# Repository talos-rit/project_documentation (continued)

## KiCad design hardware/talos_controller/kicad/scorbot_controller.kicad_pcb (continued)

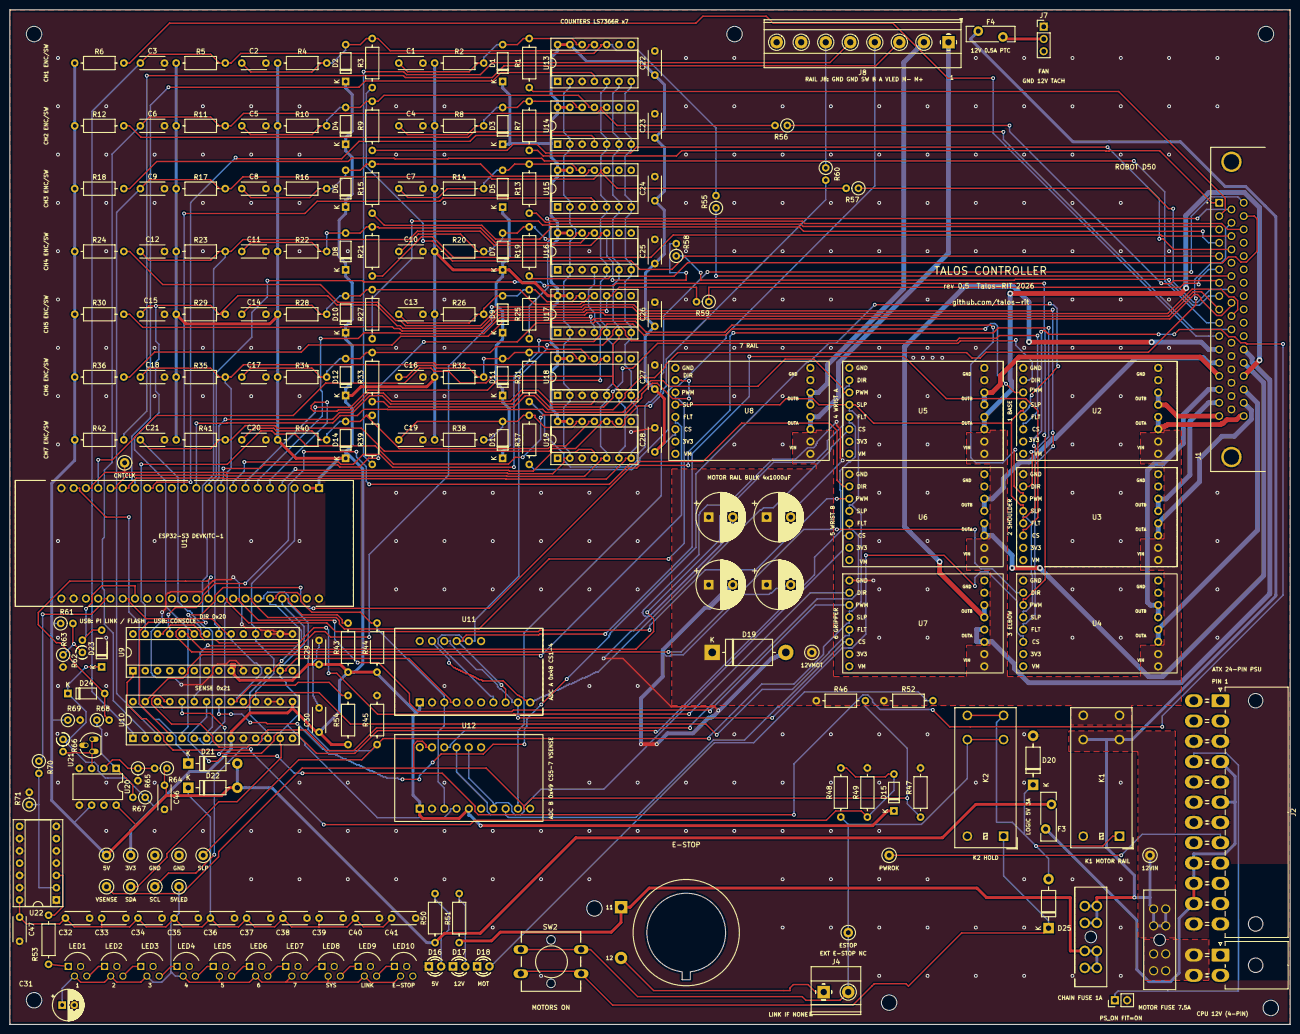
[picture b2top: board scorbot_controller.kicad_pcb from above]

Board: 2 copper layers, 265.0 x 210.0 mm, 231 parts (0 on the bottom side), 147 nets.

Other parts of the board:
H1, H2, H3, H4, H9, H10, H11: MountingHole_3.2mm_M3

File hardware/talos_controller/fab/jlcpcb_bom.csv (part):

Comment,Designator,Footprint,JLCPCB Part #,Design part (Digi-Key BOM),Note
1nF,"C1,C2,C4,C5,C7,C8,C10,C11,C13,C14,C16,C17,C19,C20",C_Disc_D5.0mm_W2.5mm_P5.00mm,C2761735,TDK FG28C0G1H102JNT06,"Dersonic CD1H102KC9BER1D100 1 nF 50 V X7R +-10 %, 5.08 mm; C20754723 (Y5P) not found; encoder RC tolerates +-30 %; verify stock"
100nF,"C22,C23,C24,C25,C26,C27,C28,C29,C30,C32,C33,C34,C35,C36,C37,C38,C39,C40,C41",C_Disc_D5.0mm_W2.5mm_P5.00mm,C254085,TDK FG28X7R1H104KNT06,"Dersonic CC1H104MC1FD3F6C10MF 100nF 50V Y5V disc, P=5.08 mm, decoupling only (19)"
100nF X7R,"C3,C6,C9,C12,C15,C18,C21,C46,C47",C_Disc_D5.0mm_W2.5mm_P5.00mm,C342794,TDK FG28X7R1H104KNT06,"the design part itself (TDK X7R, 5 mm): the switch-line RC (C3-C21), U20's (C46) and U22's (C47) decoupling; was hand-fitted only for the dielectric"
100uF 25V,C31,CP_Radial_D6.3mm_P2.50mm,C165558,Panasonic EEU-FR1E101,"SamYoung NXA25V100M6.3*11 2.5TP, 6.3 x 11 mm, 2.5 mm pitch, 105 C 5000 h: matched at order 2026-11-11, 8,132 in stock (the design part EEU-FR1E101, C264049, had 1); polarised: check the stripe in JLCPCB's placement preview"
1000uF 25V,"C42,C43,C44,C45",CP_Radial_D10.0mm_P5.00mm,C2960400,Panasonic EEU-FR1E102,"HRK CD110 25V 1000uF 10x20 mm, 5 mm pitch; alternative C231201 (Lelon RXK, 10x20). Not the 12.5 mm can"
BAT42,D15,D_DO-35_SOD27_P7.62mm_Horizontal,C2798198,Vishay BAT85,"ST BAT42 on D15 ONLY (e-stop sense node into the MCP23017: VDD+0.6 V, IIK +-20 mA); NOT on D1-D14, D23, D24; polarised: check the band end in JLCPCB's placement view"
green,"D16,D17",LED_D3.0mm,C85161,Kingbright WP710A10GD,"Everlight 204-10SYGD/S530-E3 3 mm yellow-green, 2.54 mm pitch; no sheet for it in fab/datasheets (the Kingbright sheets cover only the WP710A10 parts); check the lamp polarity in JLCPCB's placement preview (cathode = the short lead = pad 1, the square pad"
yellow,D18,LED_D3.0mm,C85160,Kingbright WP710A10YD,"Everlight 204-10UYD/S530-A3-L 3 mm yellow, stock not seen; else hand-fit the Kingbright; check the lamp polarity in JLCPCB's placement preview (cathode = the short lead = pad 1, the square pad"
1.5KE16A,D19,D_DO-201AD_P15.24mm_Horizontal,C3034403,Littelfuse 1.5KE16A,matched by JLCPCB (Sept 16); not found by the 2026-10-22 search; no substitute accepted
1N4007,"D20,D25",D_DO-41_SOD81_P10.16mm_Horizontal,C78736,onsemi 1N4007G,"MCC 1N4007-TP DO-41; D20 coil flyback, D25 K2 hold: silicon, never a Schottky; check the band end of D20 and D25 in JLCPCB's placement preview"
1N5819,D21,D_DO-41_SOD81_P10.16mm_Horizontal,C2474,onsemi 1N5819G,"MDD 1N5819 (D22 is a link, hand-fitted); polarised: check the band end in JLCPCB's placement view"
ATO holder,"F1,F2",FuseHolder_Blade_ATO_Littelfuse_FLR_178.6165,C207061,Littelfuse 178.6165.0001,"Littelfuse 178.6165.0002, the same holder as the .0001 in 500-piece packing (drawing 178.6165.0000 rev H): matched at order 2026-11-11, 2,129 in stock (C207060 had 1); the fuses (F1 028707.5PXCN, F2 0287001.PXCN) are pushed in by hand"
3 A PTC,F3,Fuse_Bourns_MF-RG400,C208487,Littelfuse RUEF300,"Bourns MF-R300 ONLY if its sheet gives R1max <= 0.08 Ohm and 5.1 mm leads (the 5 V budget used 20-80 mOhm); else hand-fit RUEF300; JLCPCB's listing gives R1max 80 mOhm and 5.1 mm leads: condition met, placed"
0.5 A PTC,F4,Fuse_Bourns_MF-RG400,C76399,Littelfuse RXEF050,the design part
E-STOP ext (NC),J4,"TerminalBlock_Phoenix_MKDS-1,5-2-5.08_1x02_P5.08mm_Horizontal",C480516,"Phoenix Contact MKDS 1,5/ 2-5,08 (1715721)","the design part: 5.08 mm, 0.9 x 0.9 mm pins, 1.3 mm hole (fab/datasheets Phoenix_Contact-1715721); matched at order 2026-11-11, 2,166 in stock; JLCPCB's automatic matcher does not assign this code even though a manual search finds it in stock: at upload, Search C480516 and Select by hand; alternatives if that bothers you: C5183929 (the same Phoenix part under a second listing) or C2915639 (the DORABO DB128V-5.08-2P, the 2-pole sibling of J8, covered by the same drawing)"
FAN 12 V,J7,PinHeader_1x03_P2.54mm_Vertical,C49257,generic PinHeader 1x03,BOOMELE 2.54-1*3P male header
RAIL,J8,"TerminalBlock_Phoenix_MKDS-1,5-8-5.08_1x08_P5.08mm_Horizontal",C5143711,"Phoenix Contact MKDS 1,5/ 8-5,08 (1715789)","DORABO DB128V-5.08-8P-GN-S, accepted on its drawing 2026-11-10 (fab/datasheets/DORABO DB128V-5.08-XXP-C-S drawing (C5143711).pdf; 2,062 in stock; the design part Phoenix 1715789 is not at LCSC and stays the hand-fit fallback (Digi-Key)"
PS_ON (fit = on),JP1,PinHeader_1x02_P2.54mm_Vertical,C32713268,generic PinHeader 1x02 + jumper,"hanxia HX PZ2.54-1x2P ZZ, straight 1x2 male header (2.5 mm insulator, 6 mm pin, 3 mm tail): matched at order 2026-11-11, 183,211 in stock; the shunt is fitted by hand"
G5RL-1A-E-HR 12V 16A,"K1,K2",Relay_SPST_Omron_G2RL-1A-E,C231374,Omron G2RL-1A-E DC12,"Omron G5RL-1A-E-HR DC12: the accepted drop-in for the design part G2RL-1A-E DC12: same footprint and coil (12 V, 360 Ohm, 33 mA), 16 A NO contact, inrush-rated (high-inrush model); matched at order 2026-11-12, 130 in stock. If the G2RL is back in stock it is equally fine. Check the relay orientation in JLCPCB's placement preview (a different model than the G2RL's); the pin pattern is asymmetric, so a wrong rotation shows as pins off the pads. Rejected lookalikes: G2RL-1A-E-CN (C469120), plain G5RL-1A-E (C122874)"
1k,"R1,R3,R7,R9,R13,R15,R19,R21,R25,R27,R31,R33,R37,R39,R50,R52,R55,R56,R57,R58,R59,R60,R69",R_Axial_DIN0207_L6.3mm_D2.5mm_P10.16mm_Horizontal; upright designators: R_Axial_DIN0207_L6.3mm_D2.5mm_P2.54mm_Vertical,C57435,Yageo MFR-25FBF52-1K,"UNI-ROYAL MFR0W4F1001A50 1 % metal film (C53431608 not found); UPRIGHT (2.54 mm pitch) designators R55,R56,R57,R58,R59,R60,R69: JLCPCB forms them on end, the placement preview shows the 2.54 mm pairs; one line since 2026-11-11 so the upload raises no duplicate-part warning (the two lines matched the same code)"
10k,"R2,R4,R5,R8,R10,R11,R14,R16,R17,R20,R22,R23,R26,R28,R29,R32,R34,R35,R38,R40,R41,R47,R49,R54,R71",R_Axial_DIN0207_L6.3mm_D2.5mm_P10.16mm_Horizontal; upright designators: R_Axial_DIN0207_L6.3mm_D2.5mm_P2.54mm_Vertical,C57436,Yageo MFR-25FBF52-10K,"UNI-ROYAL MFR0W4F1002A50 1 % (Yageo C1519255 out of stock); UPRIGHT (2.54 mm pitch) designators R71: JLCPCB forms them on end, the placement preview shows the 2.54 mm pairs; one line since 2026-11-11 so the upload raises no duplicate-part warning (the two lines matched the same code)"
47,"R6,R12,R18,R24,R30,R36,R42",R_Axial_DIN0207_L6.3mm_D2.5mm_P10.16mm_Horizontal,C58604,Yageo MFR-25FBF52-47R,"UNI-ROYAL MFR0W4F470JA50 47 Ohm (the listing says 1 % although the J in the code usually means 5 %; encoder LED series, either is fine): matched at order 2026-11-11, 4,060 in stock"
2.2k,"R43,R44,R45,R51,R66,R67",R_Axial_DIN0207_L6.3mm_D2.5mm_P10.16mm_Horizontal; upright designators: R_Axial_DIN0207_L6.3mm_D2.5mm_P2.54mm_Vertical,C58595,Yageo MFR-25FBF52-2K2,"UNI-ROYAL MFR0W4F2201A50 1 %: matched at order 2026-11-11, 2,397 in stock; UPRIGHT (2.54 mm pitch) designators R66,R67: JLCPCB forms them on end, the placement preview shows the 2.54 mm pairs; one line since 2026-11-11 so the upload raises no duplicate-part warning (the two lines matched the same code)"
39k,R46,R_Axial_DIN0207_L6.3mm_D2.5mm_P10.16mm_Horizontal,C1369871,Yageo MFR-25FBF52-39K,"Yageo MFR-25FBF52-39K, the design part: matched by JLCPCB at order 2026-11-11"
30k,R48,R_Axial_DIN0207_L6.3mm_D2.5mm_P10.16mm_Horizontal,C58652,Yageo MFR-25FBF52-30K,"UNI-ROYAL MFR0W4F3002A50, title only: confirm value and stock"
330,"R53,R70",R_Axial_DIN0207_L6.3mm_D2.5mm_P10.16mm_Horizontal; upright designators: R_Axial_DIN0207_L6.3mm_D2.5mm_P2.54mm_Vertical,C119313,Yageo MFR-25FBF52-330R,"CCO MF1/4W-330R 1 %; UPRIGHT (2.54 mm pitch) designators R70: JLCPCB forms them on end, the placement preview shows the 2.54 mm pairs; one line since 2026-11-11 so the upload raises no duplicate-part warning (the two lines matched the same code)"
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
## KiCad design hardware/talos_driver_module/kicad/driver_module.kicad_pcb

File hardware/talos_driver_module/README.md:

# Talos driver module, rev 0.1

A plug-in motor driver for the [Talos controller board](../talos_controller/README.md). It fits the controller's driver sockets
in place of a Pololu G2 18v17: the same 33 × 20 mm outline, the same sixteen pins, the same meaning on every pin the controller
uses. One module drives one brushed DC motor from the controller's 12 V motor rail. It is built from a TI DRV8701E gate driver,
two AO4882 dual MOSFETs as the H-bridge and a 20 mΩ shunt, all surface-mount on the top side of a two-layer board, so a board
house can build it complete except for the two pin strips.

The reason it exists is cost. The G2 is a 17 A general-purpose driver at about USD 45; a Scorbot joint motor needs 2 to 3 A.
Sized for that, ten assembled modules were quoted by JLCPCB on 13 November 2026 at USD 49.22 on lead-free HASL and USD 64.84 on
ENIG, before shipping: about USD 5 and USD 6.50 a module. A batch of twenty is estimated at about USD 3.40 a module.

> **Status, 13 November 2026.** First design, checked on paper only: design-rule check, the board's connections against the
> schematic, a recalculation of the copper's resistance, loops and heating, and the placement file pad by pad against JLCPCB's own
> footprints. No module has been built, powered or measured, and every figure below is a data-sheet value or an estimate. The
> files are fit for a small prototype batch, not for a robot:
> build a few, run the bench tests in section 6 next to a real G2, and only then put one on an arm. The limits and the open
> questions are in section 7.

Left to right: the logic pin row with a white bar beside it; the passives and the DRV8701E gate driver (U1); the two MOSFET
pairs Q2 and Q1 with the shunt R1 above them and the supply capacitors C1, C2 below; the power pin row. The round pads are test
points.

## What is in this folder

| File | What it is |
| --- | --- |
| `README.md` | this guide |
| `parts.md` | the parts list with the substitution rules |
| `fab/driver_module_rev0.1_gerbers.zip` and `.sha256` | the manufacturing files (Gerbers and drill files) |
| `fab/jlcpcb_bom.csv`, `fab/jlcpcb_cpl.csv` | the BOM and placement files for JLCPCB's assembly service |
| `fab/hand_assembled.csv` | what the assembly service does not place: the pin strips, the spare resistor position, the test pads |
| `schematic.pdf` | the schematic |
| `assembly_map.pdf` | every part's position with its reference and value, pin 1 marks, the pin names |
| `images/` | the board's top and bottom views and the assembly map as pictures |
| `kicad/` | the KiCad project: board, schematic, design rules, the project's footprint library. KiCad 7 format; later versions open and upgrade it |

## How it compares with the Pololu G2 18v17

| | Pololu G2 18v17 | This module |
| --- | --- | --- |
| Outline and pins | 1.3 × 0.8 in, two rows of eight | the same holes and outline |
| Supply | 6.5 to 30 V | the controller's 12 V rail (10 to 13 V); parts rated 40 V or more |
| Continuous current | 17 A | designed for 3 A, unproven: plan on 2 A until test 4 has been run (section 7) |
| Current limit | about 40 A unless a resistor is added | fixed by two resistors: 3.6 A typical, 2.5 to 4.5 A across part tolerances |
| Current-sense pin | about 20 mV/A plus about 50 mV | 19.7 mV/A plus 49 mV, by design |
| Sleep, fault, PWM and direction pins | | the same behaviour by design; the G2's published figures match the same TI driver |
| 3V3 and VM pins | outputs | pins present, not connected |
| Reverse-supply protection | yes | none |
| Over-temperature protection of the MOSFETs | none | none |
| Status | a tested product | untested |

What you give up is headroom and a proven product. The G2's MOSFETs are far larger than a Scorbot needs, which is what makes it
forgiving; this module has a few amps of margin, no more. It suits this controller and these motors, not a general 17 A job.

## 1. Order the boards

Upload `fab/driver_module_rev0.1_gerbers.zip` to JLCPCB as it is (check it against the `.sha256` file if it was copied around).

| Option | Choose |
| --- | --- |
| Layers, size | 2 layers; 33.02 × 20.32 mm is read from the files |
| Thickness, copper | 1.6 mm, 1 oz |
| Colour | green: the Economic assembly service offers ENIG on green boards only |
| Surface finish | ENIG gives flat pads under U1 (0.5 mm pitch) and cost USD 15.62 more for ten in our quote. Lead-free HASL is the cheaper choice and within what JLCPCB states for this pitch |
| Mark on PCB | have the order number left off, or put on the underside; the top has no room for it |
| Quantity | 5 is the minimum for bare boards; the Economic assembly service takes 2 to 50 |

**Assembly.** Tick PCB assembly, Economic, top side. Before paying, check that the quote page says "Economic PCBA Price": our
first quote had slipped to the Standard service, which charged about USD 36 more for the same ten modules. No panel, edge rails or fiducials are needed for a board this size. Upload
`fab/jlcpcb_bom.csv` as the BOM and `fab/jlcpcb_cpl.csv` as the placement file; every BOM line carries a JLCPCB part number.
Three part types are from the Extended library (U1, the MOSFETs, the shunt), which adds a fee per type.

**Check the placement preview before paying.** A chip turned by a quarter turn passes every automatic check and ruins the
batch. In the preview, the pin 1 dot of U1, Q1 and Q2 must sit where `assembly_map.pdf` has its red dots: for U1 the corner
nearest C3, for Q1 and Q2 the pad at the triangle on the silkscreen. The rotations in the placement file were computed from
JLCPCB's own library footprints for these parts (as they were on 13 November 2026), but the preview is the final word. Order the
files as they are: if a part is substituted in the order form, look at the preview again.

## 2. Parts

`parts.md` lists every part. The assembly service fits all of them except the two 1 × 8 pin strips, which you buy and solder
yourself. The position R3B stays empty.

## 3. Assemble

1. Push the two pin strips into a spare socket or a breadboard, long pins down, so they stand square and at the right spacing.
2. Lay the module on them, parts up. The silkscreen names each pin on both sides; the logic row is the side with the small parts.
3. Solder all sixteen pins from the top.
4. Look at the three chips under a magnifier for solder bridges before the first power.

Fitted this way the module stands about 11 mm above the controller, as a G2 on its own headers does.

**Before the first power.** Under a magnifier on every assembled module: U1's dot at the corner nearest C3, the dots of Q1 and Q2
at their triangles, no solder bridge along U1's four rows. With a multimeter: no short from GND to VIN, to OUTA or to OUTB. Then
power it for the first time from a bench supply with a current limit.

**Finding the test pads.** Only TP2, TP3 and TP5 are named on the board. The label "R3B" above the pad at the lower left
belongs to the empty resistor position beside it; that pad is TP6. The assembly map names every pad.

**Plugging a module in.** A module turned round still fits the socket, and so does one shifted by a pin; either destroys it,
or shorts the motor rail, the moment the rail comes on. With the rail off: the logic row (the white bar on the top of the
module runs along it, beside its pin names) goes to the socket's logic row, every pin sits in its own hole with none hanging
out, then power. Pull a module out by its two short ends, where the pins are; three small parts that set the current limit sit
close to one long edge.

## 4. Pins

Logic row, in socket order:

| Pin | Direction | What it does |
| --- | --- | --- |
| GND | | ground, common with the power row |
| DIR | in | direction: high drives OUTA high and OUTB low |
| PWM | in | 3.3 V logic. High drives the motor, low brakes it (both outputs low). 20 kHz in the firmware; the driver accepts up to 100 kHz and 100 % duty |
| SLP | in | low puts the driver to sleep: outputs open, under 15 µA from the rail at room temperature (data sheet). The module has no pull-up; the controller drives the line and holds it low at rest |
| FLT | out | open drain, low while the driver reports a fault. Never driven high; the controller supplies the pull-up |
| CS | out | motor current while driving: 19.7 mV/A plus 49 mV. 0 V while braking and asleep |
| 3V3 | | not connected |
| VM | | not connected |

Power row: GND (two pins), OUTB (two), OUTA (two), VIN (two).

## 5. Firmware

Nothing changes against a G2. The controller firmware keeps its defaults: PWM 20 kHz, current sense 20 mV/A with a 50 mV offset,
and the 5 % minimum duty for a current reading (`SC_PWM_FREQ_HZ`, `SC_CS_MV_PER_A`, `SC_CS_OFFSET_MV`, `SC_CS_MIN_DUTY_PCT` in
`idf.py menuconfig`). Modules and G2s can share a board.

**R3A or R3B.** The current-sense pin needs its 50 mV offset from somewhere. R3A takes it from the PWM pin, so the offset is there
only while the bridge drives and the pin reads 0 V in the PWM off-time: this is what the firmware assumes, and it is the fitted
position. R3B takes it from the driver's 3.3 V supply, so the offset stays through the off-time: this is what TI's data sheet
suggests a real G2 does. Measure a real G2 first (test 1 below). If it holds its offset in the off-time, the firmware's current
model has to change for the G2 anyway, and a batch of modules is then built with R3B fitted instead of R3A. Never fit both.

## 6. Bench tests before first use

Do these with one module and one real G2 side by side in a controller, each on the same type of motor, with a clamp meter on a
motor lead and an oscilloscope. Start from a bench supply with a current limit, not from the ATX supply. Never plug a module
into a live rail. Do the edge check of test 2 at a low current before anything that reaches the current limit (tests 3 to 5).

| Test | What to do | Expect |
| --- | --- | --- |
| 1. Current-sense pin and supply | On the G2 first: scope CS at 25, 50 and 100 % duty, at rest and at 2 A, during the on-time and the off-time. Then the same on the module, up to 4 A. While the module drives 3 A, also scope the supply across its VIN and GND pins | Module: 19.7 mV/A ± 3 % plus 49 mV while driving, under 2 mV in the off-time. Note what the G2 does in the off-time (section 5). Supply at the module: ripple under about 0.1 V at the PWM frequency, ringing of a few tenths of a volt after each edge (estimates); much more means the module needs a capacitor of its own |
| 2. Direction, brake and edges | DIR high and low, PWM at 0, 50 and 100 %. Then, at the current limit, scope U1's pins 18 and 23 (the switch nodes) and pin 21 (the sense input) against U1's centre pad with a short spring ground | Same motor direction as the G2; both outputs low with PWM low. The switch nodes stay above −2 V and the sense input within ±1 V at the edges; if not, the gate drive has to be slowed (R6) before the module is used |
| 3. Current limit | Stall the motor at 100 % duty with a current probe on the lead | The current holds between 2.5 and 4.5 A (3.6 A typical). Write the figure on the module |
| 4. Temperature | 3 A for 30 minutes inside the enclosure, in both directions (DIR low first: it is expected to run hotter), with a thermocouple on Q2's pins 5 and 6, once with warm modules in the neighbouring sockets. Then a 5-minute stall at 70 % duty | MOSFET case under 120 °C; no fault. This test decides the continuous rating. If the stall runs hotter, the firmware's stall detection is what protects the module |
| 5. Faults | From the current-limited supply, with the scope on test pad TP4 (the top of the shunt): short OUTA to OUTB through a switch; lower the supply below 6 V | FLT goes low and the firmware reports a driver fault; FLT releases afterwards; no damage. If TP4 peaks above 1 V in the short, change R8 to 100 Ω before going further |
| 6. Sleep and power-up | Switch SLP a hundred times with the rail on; switch the rail on and off with SLP low and with SLP high; watch FLT on the scope | Outputs open and CS at 0 V asleep. Record every FLT pulse: the driver pulls FLT low while its supply is under about 6 V, and the firmware must not treat that as a fault |
| 7. Back-drive | With SLP low, turn the motor fast by hand | Nothing but a small rise of the rail; module undamaged |

## 7. Limits and open questions

- **Nothing has been built.** The first batch is the first test of every footprint and of the layout.
- **3 A continuous is unproven.** A simple estimate puts the hottest MOSFET junction at about 95 °C at 3 A and 40 °C ambient. A
  model of the routed copper puts it at 105 to 128 °C when no heat leaves through the pins, higher still in dead air between
  neighbours, and at 87 to 102 °C when the pins carry heat into the controller. Neither is a measurement; test 4 is. Until it has
  been run, treat the module as a 2 A part; the controller firmware's per-joint current limits are 1.5 to 2.0 A.
- **The current limit of a given module lies between 2.5 and 4.5 A.** At the top of that range a held stall is estimated to
  overheat the MOSFETs within about two minutes, so the firmware's stall and over-current detection are part of the protection.
- **No over-temperature protection of the MOSFETs.** The driver chip shuts down at 150 °C of its own die only. The G2 is the same.
- **A short from an output to ground is detected only above roughly 28 to 65 A.** A partial short to the robot's frame can destroy a MOSFET
  without a fault report. A short across the motor is detected.
- **No large capacitor on the module.** A G2 carries a 150 µF electrolytic, the tall cylinder on most driver boards. This module
  has only ceramic capacitors (C1, C2, C10, C11) and relies on the controller's four 1000 µF capacitors, which sit on the motor
  rail a few centimetres from the sockets. By estimate the supply ripple at the module is under 0.1 V; test 1 measures it. Used
  anywhere but in this controller, the module needs a few hundred µF close to its VIN and GND pins.
- **No reverse-supply protection.** A bench supply can be connected backwards, and a module plugged in turned round sees the
  rail backwards (section 3). A G2 survives that; this module does not.
- **The FLT line during power-up.** The driver holds FLT low while the motor rail is below about 6 V, which happens at every
  MOTORS ON, e-stop and rail decay. The G2 is expected to do the same. Ignoring FLT while the drives are off is not yet
  implemented in the controller firmware.
- **The current reading includes the ground drop of the socket contacts,** on this module and on a G2 alike. If it matters, the
  cure is a per-board scale in the firmware.
- **Second sources.** The DRV8701E is a TI part with no equivalent. The AO4882 has pin-compatible copies with different
  on-resistance; see `parts.md` before substituting.

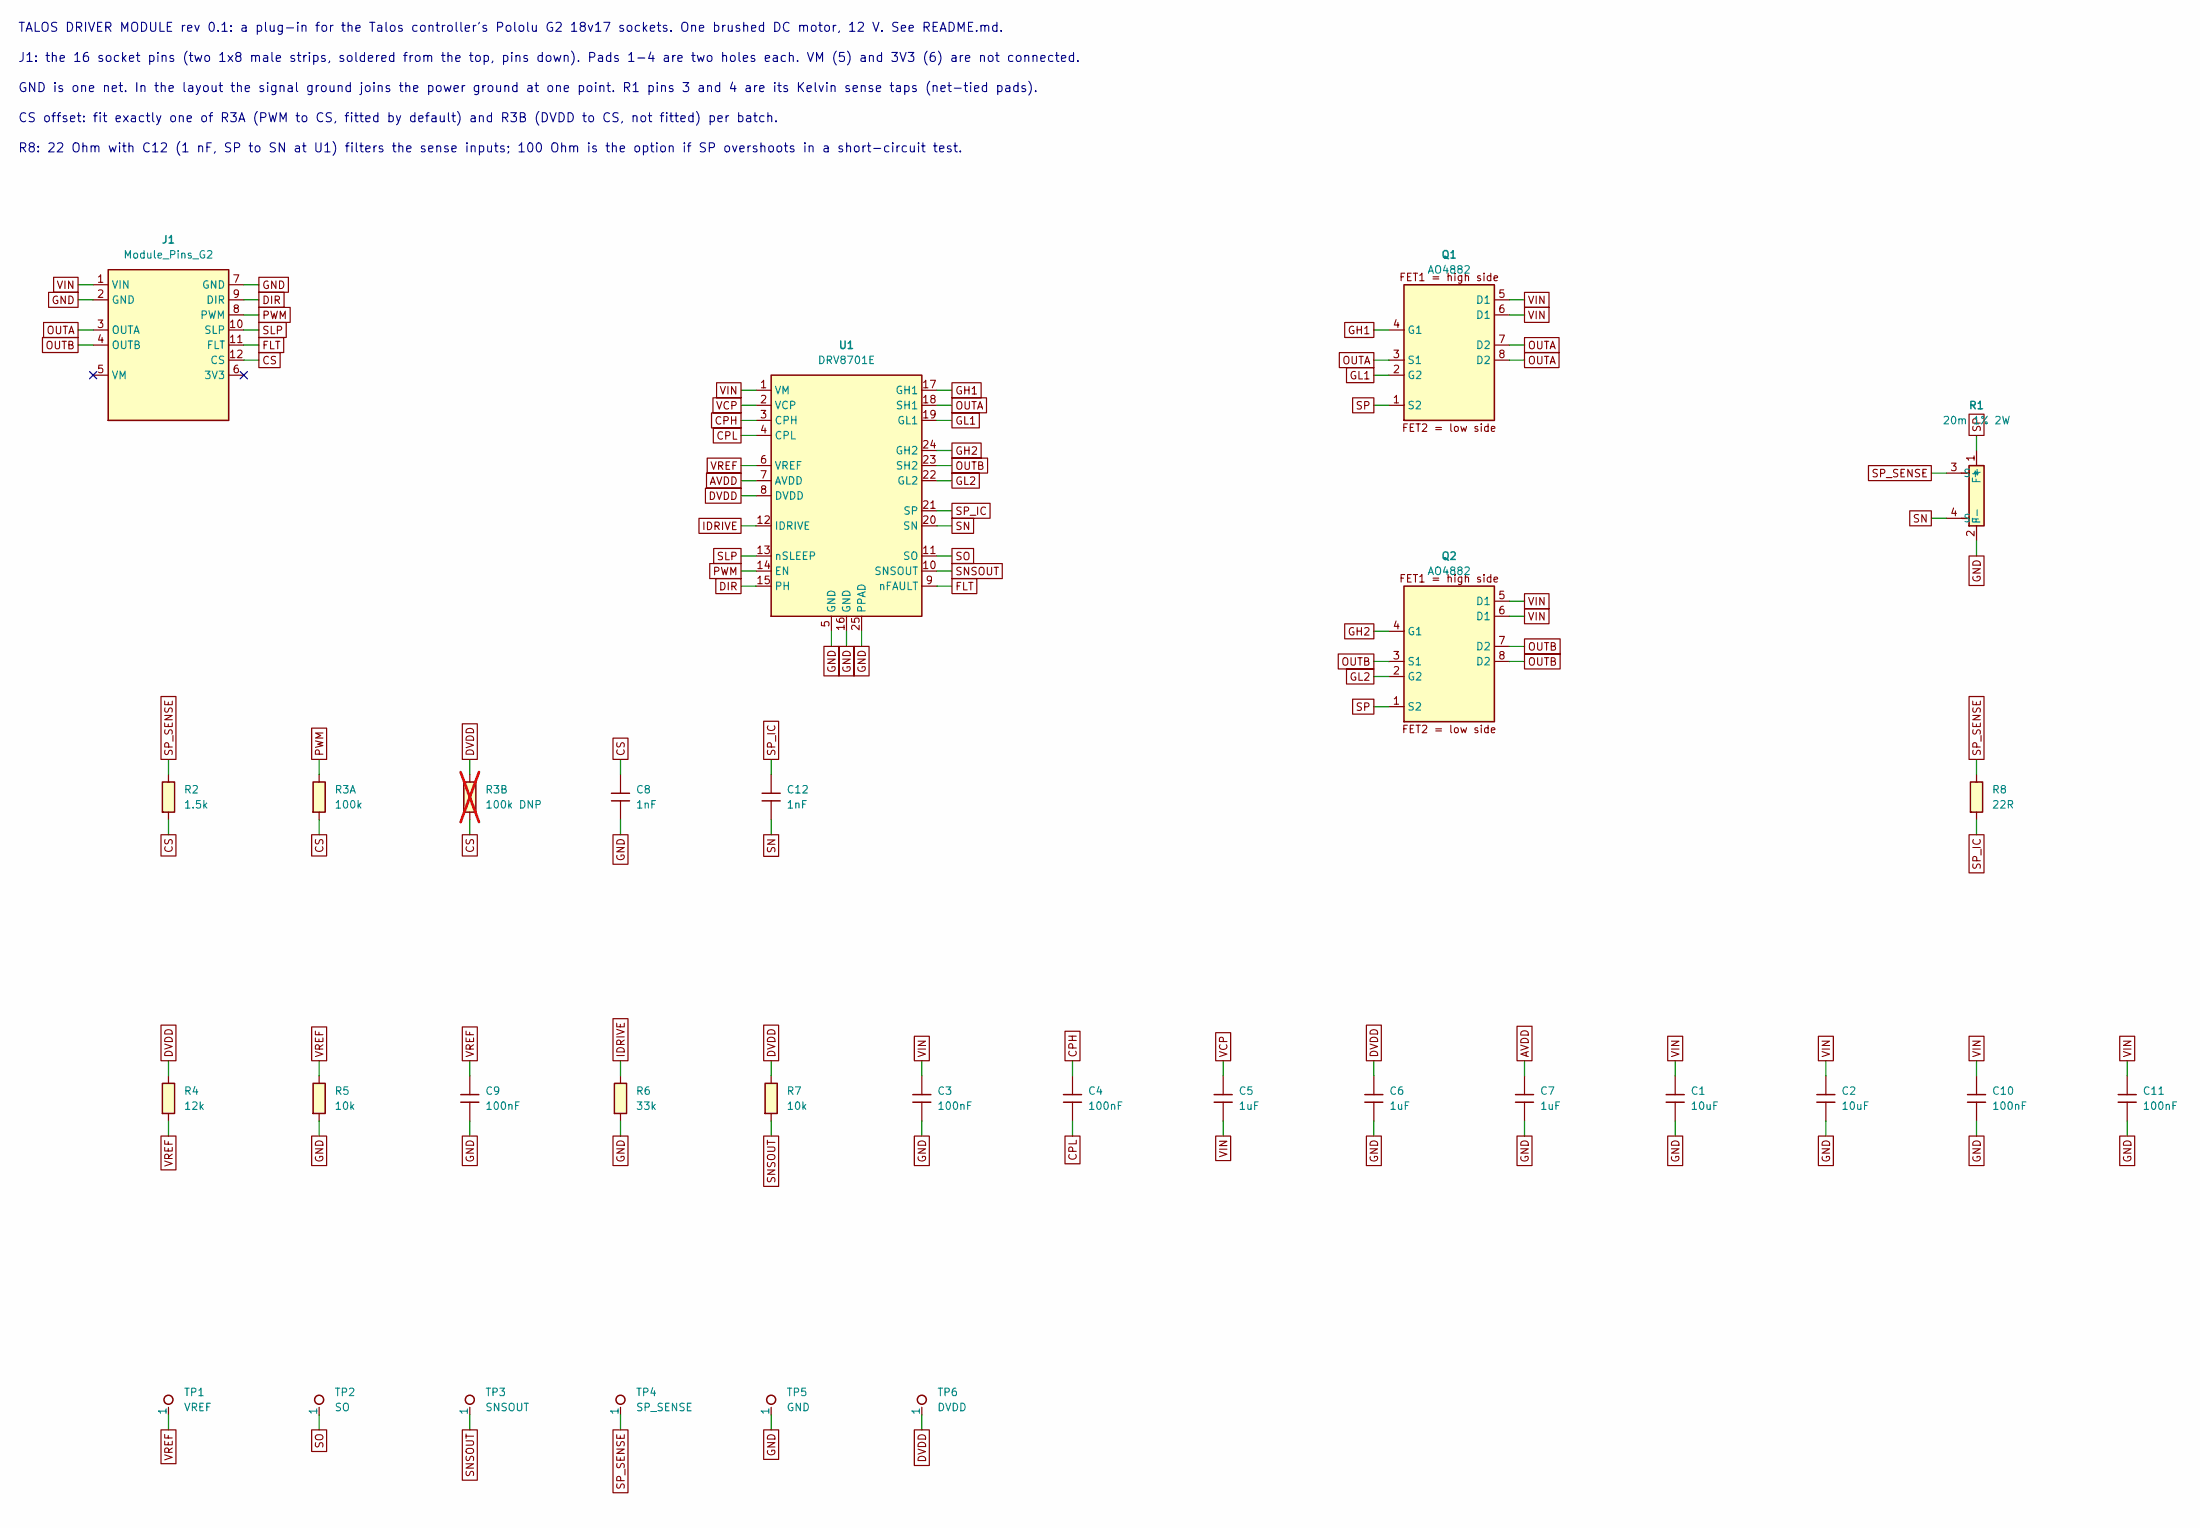
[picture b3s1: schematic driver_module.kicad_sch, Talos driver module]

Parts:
C1, C2: 10uF; C_1206_3216Metric; MPN CL31A106KBHNNNE; LCSC C13585
C3, C4, C9, C10, C11: 100nF; C_0603_1608Metric; MPN CC0603KRX7R9BB104; LCSC C14663
C5, C6, C7: 1uF; C_0603_1608Metric; MPN CL10A105KB8NNNC; LCSC C15849
C8, C12: 1nF; C_0603_1608Metric; MPN CL10B102KB8NNNC; LCSC C1588
J1: Module_Pins_G2
Q1, Q2: AO4882; SOIC-8_3.9x4.9mm_P1.27mm; MPN AO4882; LCSC C477943
R1: 20m 1% 2W; R_2512_Kelvin; MPN FMF25FPJR020-LH; LCSC C105360
R2: 1.5k; R_0603_1608Metric; MPN 0603WAF1501T5E; LCSC C22843
R3A: 100k; R_0603_1608Metric; MPN 0603WAF1003T5E; LCSC C25803
R3B: 100k DNP; R_0603_1608Metric; MPN 0603WAF1003T5E; LCSC C25803; not fitted
R4: 12k; R_0603_1608Metric; MPN 0603WAF1202T5E; LCSC C22790
R5, R7: 10k; R_0603_1608Metric; MPN 0603WAF1002T5E; LCSC C25804
R6: 33k; R_0603_1608Metric; MPN 0603WAF3302T5E; LCSC C4216
R8: 22R; R_0603_1608Metric; MPN 0603WAF220JT5E; LCSC C23345
TP1: VREF; TestPoint_Pad_D1.5mm
TP2: SO; TestPoint_Pad_D1.5mm
TP3: SNSOUT; TestPoint_Pad_D1.5mm
TP4: SP_SENSE; TestPoint_Pad_D1.5mm
TP5: GND; TestPoint_Pad_D1.5mm
TP6: DVDD; TestPoint_Pad_D1.5mm
U1: DRV8701E; Texas_RGE0024F_VQFN-24-1EP_4x4mm_P0.5mm_EP2.8x2.8mm; MPN DRV8701ERGER; LCSC C90964

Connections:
AVDD: C7.1, U1.7 (AVDD)
CPH: C4.1, U1.3 (CPH)
CPL: C4.2, U1.4 (CPL)
CS: C8.1, J1.12 (CS), R2.2, R3A.2, R3B.2
DIR: J1.9 (DIR), U1.15 (PH)
DVDD: C6.1, R3B.1, R4.1, R7.1, TP6.1, U1.8 (DVDD)
FLT: J1.11 (FLT), U1.9 (nFAULT)
GH1: Q1.4 (G1), U1.17 (GH1)
GH2: Q2.4 (G1), U1.24 (GH2)
GL1: Q1.2 (G2), U1.19 (GL1)
GL2: Q2.2 (G2), U1.22 (GL2)
GND: C1.2, C2.2, C3.2, C6.2, C7.2, C8.2, C9.2, C10.2, C11.2, J1.2 (GND), J1.7 (GND), R1.2 (F-), R5.2, R6.2, TP5.1, U1.5 (GND), U1.16 (GND), U1.25 (PPAD)
IDRIVE: R6.1, U1.12 (IDRIVE)
OUTA: J1.3 (OUTA), Q1.3 (S1), Q1.7 (D2), Q1.8 (D2), U1.18 (SH1)
OUTB: J1.4 (OUTB), Q2.3 (S1), Q2.7 (D2), Q2.8 (D2), U1.23 (SH2)
PWM: J1.8 (PWM), R3A.1, U1.14 (EN)
SLP: J1.10 (SLP), U1.13 (nSLEEP)
SN: C12.2, R1.4 (S-), U1.20 (SN)
SNSOUT: R7.2, TP3.1, U1.10 (SNSOUT)
SO: TP2.1, U1.11 (SO)
SP: Q1.1 (S2), Q2.1 (S2), R1.1 (F+)
SP_IC: C12.1, R8.2, U1.21 (SP)
SP_SENSE: R1.3 (S+), R2.1, R8.1, TP4.1
VCP: C5.1, U1.2 (VCP)
VIN: C1.1, C2.1, C3.1, C5.2, C10.1, C11.1, J1.1 (VIN), Q1.5 (D1), Q1.6 (D1), Q2.5 (D1), Q2.6 (D1), U1.1 (VM)
VREF: C9.1, R4.2, R5.1, TP1.1, U1.6 (VREF)

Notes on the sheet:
TALOS DRIVER MODULE rev 0.1: a plug-in for the Talos controller's Pololu G2 18v17 sockets. One brushed DC motor, 12 V. See README.md.
J1: the 16 socket pins (two 1x8 male strips, soldered from the top, pins down). Pads 1-4 are two holes each. VM (5) and 3V3 (6) are not connected.
GND is one net. In the layout the signal ground joins the power ground at one point. R1 pins 3 and 4 are its Kelvin sense taps (net-tied pads).
CS offset: fit exactly one of R3A (PWM to CS, fitted by default) and R3B (DVDD to CS, not fitted) per batch.
R8: 22 Ohm with C12 (1 nF, SP to SN at U1) filters the sense inputs; 100 Ohm is the option if SP overshoots in a short-circuit test.

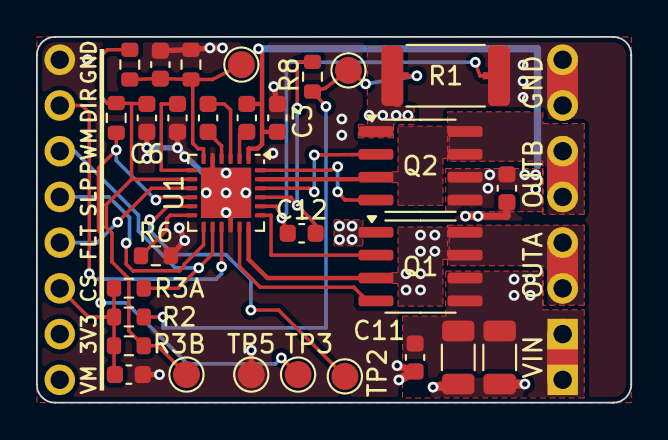
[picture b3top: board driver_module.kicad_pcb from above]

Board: 2 copper layers, 33.0 x 20.3 mm, 31 parts (0 on the bottom side), 26 nets.

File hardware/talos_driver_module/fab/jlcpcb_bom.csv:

Comment,Designator,Footprint,JLCPCB Part #
10uF,"C1,C2",C_1206_3216Metric,C13585
100nF,"C3,C4,C9,C10,C11",C_0603_1608Metric,C14663
1uF,"C5,C6,C7",C_0603_1608Metric,C15849
1nF,"C8,C12",C_0603_1608Metric,C1588
AO4882,"Q1,Q2",SOIC-8_3.9x4.9mm_P1.27mm,C477943
20m 1% 2W,R1,R_2512_Kelvin,C105360
1.5k,R2,R_0603_1608Metric,C22843
100k,R3A,R_0603_1608Metric,C25803
12k,R4,R_0603_1608Metric,C22790
10k,"R5,R7",R_0603_1608Metric,C25804
33k,R6,R_0603_1608Metric,C4216
22R,R8,R_0603_1608Metric,C23345
DRV8701E,U1,Texas_RGE0024F_VQFN-24-1EP_4x4mm_P0.5mm_EP2.8x2.8mm,C90964
